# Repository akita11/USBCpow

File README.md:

# USBCpow

USB Type-Cから5Vを供給するボードです。オプションで3.3Vレギュレータを載せて、3.3Vも出力することができます。

なお実際に供給できる電流は、給電側（USB ACアダプタやモバイルバッテリ）の性能に依存します。また3.3V出力は600mAまでです。

完成品はスイッチサイエンス等で委託販売中です。[5V版](https://www.switch-science.com/products/6434) / [5V/3.3V版](https://www.switch-science.com/products/6435)

# 使い方

+5V（および+3.3V）、GNDの端子にビニール線やピンヘッダやソケットをとりつけ、回路に電源を供給します。

以下のようにGNDと+5V（または+3.3V）に2ピンのピンヘッダをとりつけることで、ブレッドボードの電源ラインへの給電につかうことができます。

以下のようにUSBコネクタ脇の穴に1ピンのピンヘッダをとりつけることで、ブレッドボードにしっかり固定することができます。

# 作り方・必要部品

- [USB Type-Cコネクタ(6極)](https://www.aitendo.com/product/17279) 1個
- [チップ抵抗 5.1kΩ(1608サイズ)](https://www.aitendo.com/product/9962) 2個 ※R1,R2のところに実装
- 用途にあわせて、[ピンヘッダ5p](https://www.aitendo.com/product/1798)（出力部に取り付ける場合のみ）など

以下、3.3V出力を作る場合の追加部品
- [レギュレータLM1117-3.3（または互換品）](https://www.aitendo.com/product/13388) 1個
- [チップコンデンサ 10uF(1608サイズ)/10V以上](https://www.aitendo.com/product/6985) 2個 ※C1,C2のところに実装

# Author

Junichi Akita (akita@ifdl.jp, @akita11)

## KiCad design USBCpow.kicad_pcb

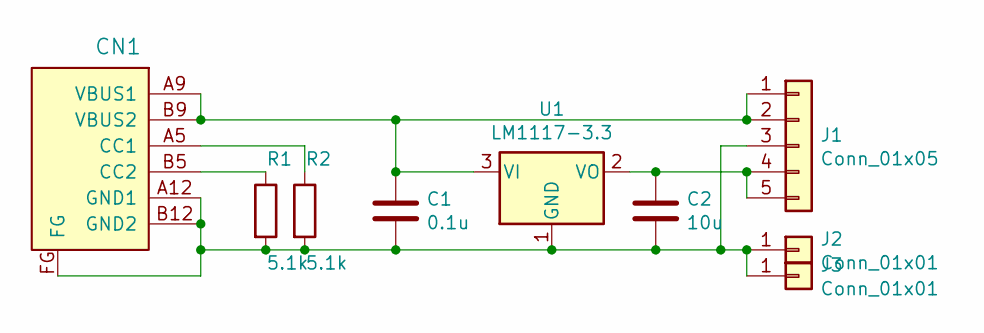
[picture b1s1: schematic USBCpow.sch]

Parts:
C1: 0.1u; C_0603_1608Metric_Pad1.05x0.95mm_HandSolder
C2: 10u; C_0603_1608Metric_Pad1.05x0.95mm_HandSolder
CN1: CON_USB-C-6; USB-C_6P
J1: Conn_01x05; PinHeader_1x05_P2.54mm_Vertical
J2, J3: Conn_01x01; PinHeader_1x01_P2.54mm_Vertical
R1, R2: 5.1k; R_0603_1608Metric_Pad1.05x0.95mm_HandSolder
U1: LM1117-3.3; SOT-223-3_TabPin2

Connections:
unnamed: C1.1, CN1.A9 (VBUS1), CN1.B9 (VBUS2), J1.1, J1.2, U1.3 (VI)
unnamed: C1.2, C2.2, CN1.A12 (GND1), CN1.B12 (GND2), CN1.FG, J1.3, J2.1, J3.1, R1.2, R2.2, U1.1 (GND)
unnamed: C2.1, J1.4, J1.5, U1.2 (VO)
unnamed: CN1.A5 (CC1), R2.1
unnamed: CN1.B5 (CC2), R1.1

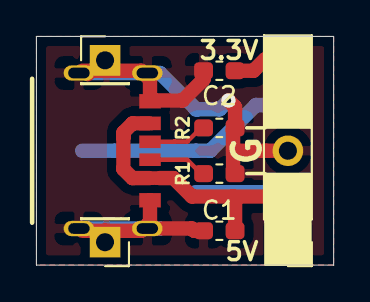
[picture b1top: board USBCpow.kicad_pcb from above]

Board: 2 copper layers, 16.5 x 12.7 mm, 9 parts (1 on the bottom side), 5 nets.

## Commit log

2020-05-28 写真の追加
2020-05-28 写真サイズの変更
2020-06-14 USBコネクタのTHもペーストを追加＆発注用BOMの追加
2020-06-18 READMEに出力電流について追記
2020-06-27 固定用ピンヘッダの穴を追加
2023-05-15 add usage
2023-05-15 add link to SS
2023-05-15 fix filename typo
2023-05-15 move usage section
2023-05-15 replace usage4 photo
